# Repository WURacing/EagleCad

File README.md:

View this project on [CADLAB.io](https://cadlab.io/project/1317). 

# EagleCad
Version Control for EagleCad files

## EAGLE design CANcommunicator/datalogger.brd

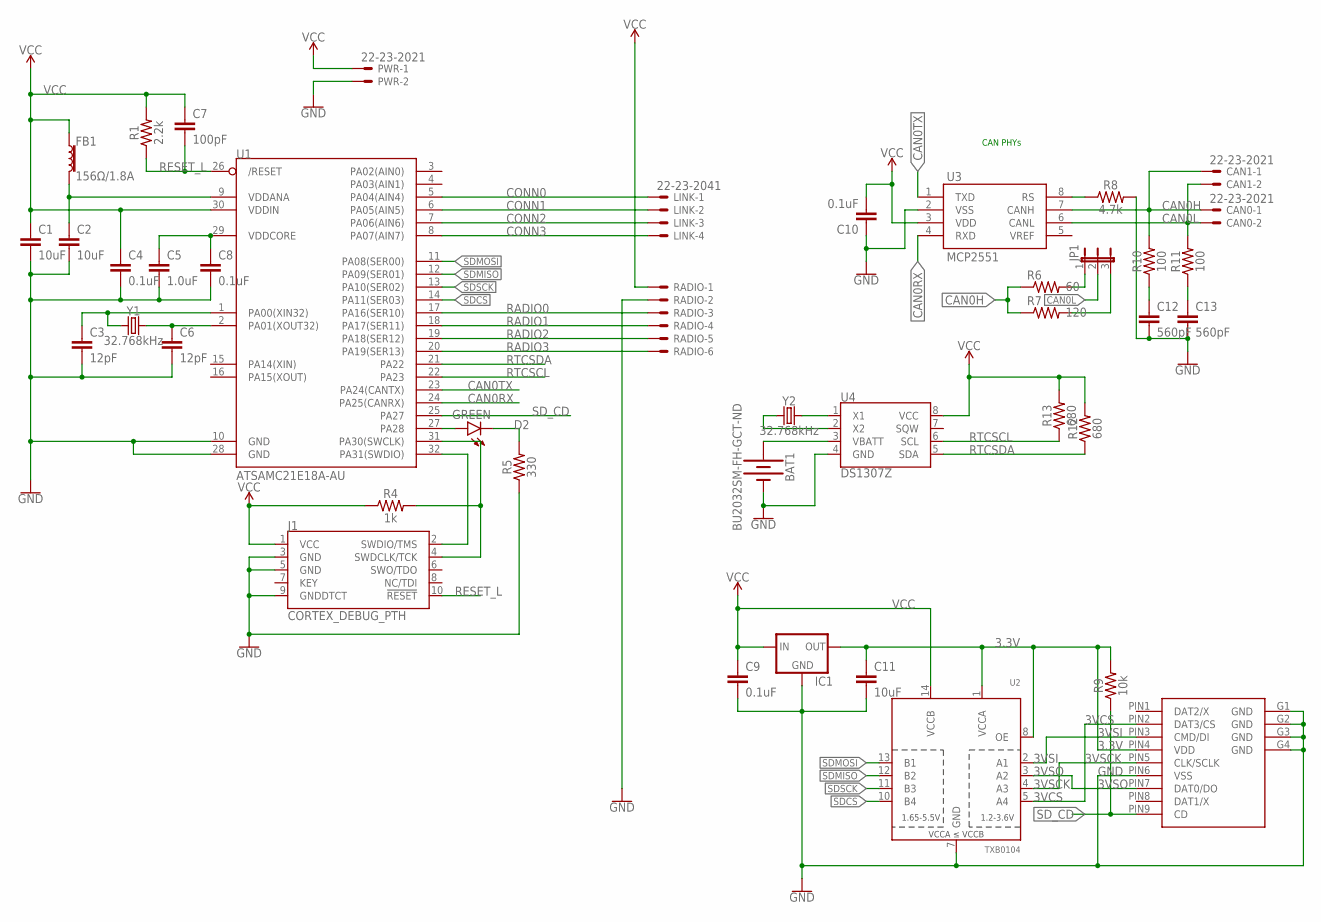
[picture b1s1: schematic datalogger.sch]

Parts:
BAT1: BU2032SM-FH-GCT-ND; BAT_BU2032SM-BT-GTR
C1, C2, C11: 10uF; 0603
C3, C6: 12pF; 0603
C4, C8, C9, C10: 0.1uF; 0603
C5: 1.0uF; 0603
C7: 100pF; 0603
C12, C13: 560pF; 0603
CAN0, CAN1: 22-23-2021
D2: GREEN; LED_3MM
FB1: 156Ω/1.8A; 0603
IC1: 78LXX
J1: CORTEX_DEBUG_PTH; 2X5-PTH-1.27MM
JP1: JP2E; JP2
LINK: 22-23-2041
PWR: 22-23-2021
R1: 2.2k; 0603
R4: 1k; 0603
R5: 330; 0603
R6: 60; R0603
R7: 120; R0603
R8: 4.7k; 0603
R9: 10k; 0603
R10, R11: 100; 0603
R12, R13: 680; 0603
RADIO: 22-23-2061
SD1: WM14405CT-ND; 1051620001-SMD
U1: ATSAMC21E18A-AU; TQFP32-08
U2: TXB0104; TSSOP14
U3: MCP2551; SO08
U4: DS1307Z; SO08-0.15
Y1, Y2: 32.768kHz; CRYSTAL-PTH-2X6-CYL

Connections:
3.3V: C11.1, IC1.OUT, R9.2, SD1.PIN4 (VDD), U2.1 (VCCA), U2.8 (OE)
3VCS: SD1.PIN2 (DAT3/CS), U2.5 (A4)
3VSCK: SD1.PIN5 (CLK/SCLK), U2.4 (A3)
3VSI: SD1.PIN3 (CMD/DI), U2.2 (A1)
3VSO: SD1.PIN7 (DAT0/DO), U2.3 (A2)
C1HRC: C12.1, R10.1
C1LRC: C13.1, R11.1
C1RS: R8.1, U3.8 (RS)
CAN0H: CAN0.1, CAN1.1, R6.1, R7.1, R10.2, U3.7 (CANH)
CAN0L: CAN0.2, CAN1.2, JP1.2, R11.2, U3.6 (CANL)
CAN0RX: U1.24 (PA25(CANRX)), U3.4 (RXD)
CAN0TX: U1.23 (PA24(CANTX)), U3.1 (TXD)
CONN0: LINK.1, U1.5 (PA04(AIN4))
CONN1: LINK.2, U1.6 (PA05(AIN5))
CONN2: LINK.3, U1.7 (PA06(AIN6))
CONN3: LINK.4, U1.8 (PA07(AIN7))
GND: BAT1.2 (-), C1.2, C2.2, C3.2, C4.2, C5.2, C6.2, C8.2, C9.2, C10.1, C11.2, C12.2, C13.2, IC1.GND, J1.3 (GND), J1.5 (GND), J1.9 (GNDDTCT), PWR.2, R5.1, R8.2, RADIO.2, SD1.G1 (GND), SD1.G2 (GND), SD1.G3 (GND), SD1.G4 (GND), SD1.PIN6 (VSS), U1.10 (GND), U1.28 (GND), U2.7 (GND), U3.2 (VSS), U4.4 (GND)
LEDA: D2.A, U1.27 (PA28)
LEDC: D2.K (C), R5.2
unnamed: BAT1.1 (+), U4.3 (VBATT)
unnamed: U4.1 (X1), Y2.2
unnamed: JP1.1, R6.2
unnamed: U4.2 (X2), Y2.1
unnamed: JP1.3, R7.2
RADIO0: RADIO.3, U1.17 (PA16(SER10))
RADIO1: RADIO.4, U1.18 (PA17(SER11))
RADIO2: RADIO.5, U1.19 (PA18(SER12))
RADIO3: RADIO.6, U1.20 (PA19(SER13))
RESET_L: C7.2, J1.10 (!RESET), R1.1, U1.26 (/RESET)
RTCSCL: R13.1, U1.22 (PA23), U4.6 (SCL)
RTCSDA: R12.1, U1.21 (PA22), U4.5 (SDA)
SDCS: U1.14 (PA11(SER03)), U2.10 (B4)
SDMISO: U1.12 (PA09(SER01)), U2.12 (B2)
SDMOSI: U1.11 (PA08(SER00)), U2.13 (B1)
SDSCK: U1.13 (PA10(SER02)), U2.11 (B3)
SD_CD: R9.1, SD1.PIN9 (CD), U1.25 (PA27)
SWDCLK: J1.4 (SWDCLK/TCK), R4.2, U1.31 (PA30(SWCLK))
SWDIO: J1.2 (SWDIO/TMS), U1.32 (PA31(SWDIO))
VCC: C1.1, C4.1, C7.1, C9.1, C10.2, FB1.1, IC1.IN, J1.1 (VCC), PWR.1, R1.2, R4.1, R12.2, R13.2, RADIO.1, U1.30 (VDDIN), U2.14 (VCCB), U3.3 (VDD), U4.8 (VCC)
VDDANA1: C2.1, FB1.2, U1.9 (VDDANA)
VDDCORE: C5.1, C8.1, U1.29 (VDDCORE)
XIN32: C3.1, U1.1 (PA00(XIN32)), Y1.1
XOUT32: C6.1, U1.2 (PA01(XOUT32)), Y1.2

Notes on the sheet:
CAN PHYs

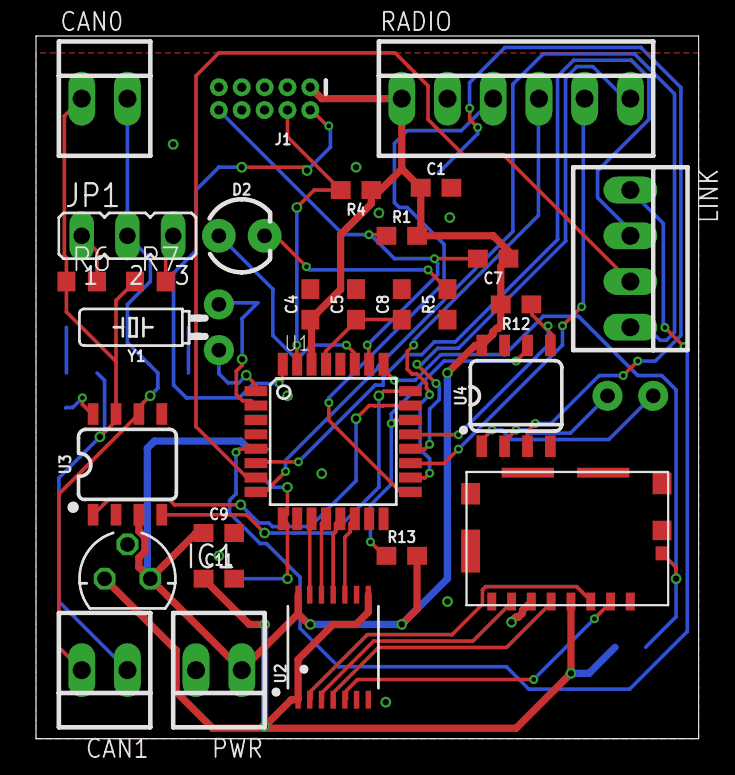
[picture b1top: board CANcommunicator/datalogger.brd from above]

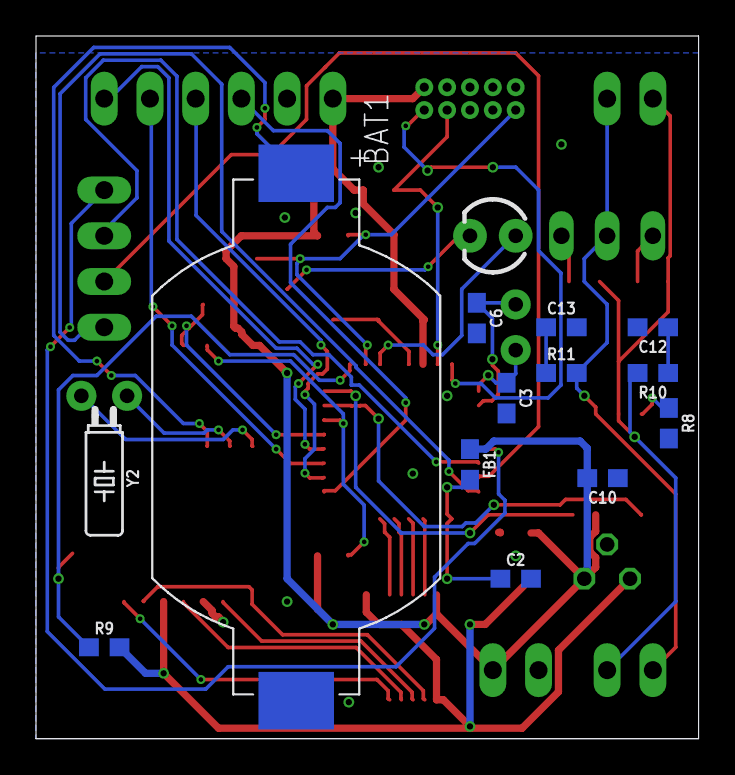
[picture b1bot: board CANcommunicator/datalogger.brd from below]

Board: 2 copper layers, 36.8 x 39.0 mm, 42 parts (13 on the bottom side), 43 nets.

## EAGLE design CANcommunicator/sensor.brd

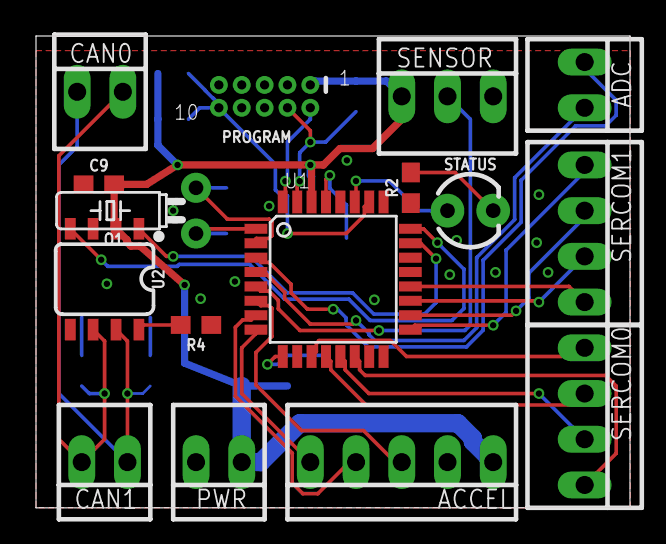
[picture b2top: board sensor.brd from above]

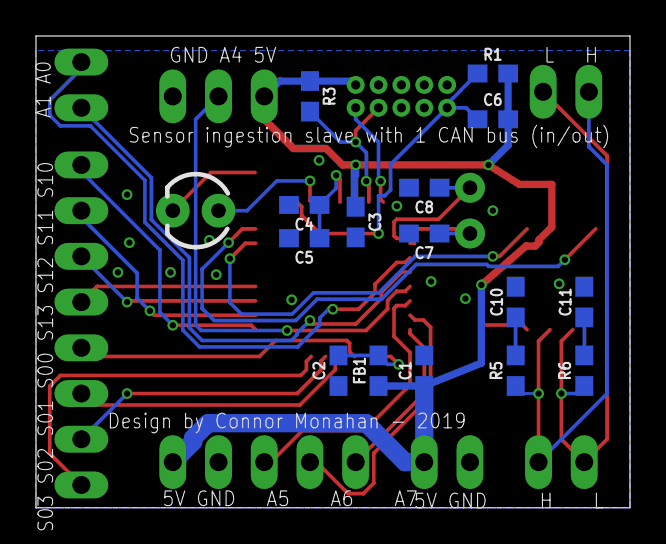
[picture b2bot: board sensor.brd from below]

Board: 2 copper layers, 33.0 x 26.2 mm, 31 parts (15 on the bottom side), 32 nets.

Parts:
ACCEL: 22-23-2051
ADC: 22-23-2021
C1, C2: 10uF; 0603
C3, C5, C9: 0.1uF; 0603
C4: 1.0uF; 0603
C6: 100pF; 0603
C7, C8: 12pF; 0603
C10, C11: 560pF; 0603
CAN0, CAN1: 22-23-2021
FB1: 156Ω/1.8A; 0603
O1: 32.768kHz; CRYSTAL-PTH-2X6-CYL
PROGRAM: CORTEX_DEBUG_PTH; 2X5-PTH-1.27MM
PWR: 22-23-2021
R1: 2.2k; 0603
R2: 330; 0603
R3: 1k; 0603
R4: 4.7k; 0603
R5, R6: 100; 0603
SENSOR: 22-23-2031
SERCOM0, SERCOM1: 22-23-2041
STATUS: GREEN; LED_3MM
U1: ATSAMC21E18A-AU; TQFP32-08
U2: MCP2551; SO08

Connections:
A0: ADC.1, U1.3
A1: ADC.2, U1.4
A4: SENSOR.2, U1.5
A5: ACCEL.3, U1.6
A6: ACCEL.4, U1.7
A7: ACCEL.5, U1.8
C1HRC: C10.1, R5.1
C1LRC: C11.1, R6.1
C1RS: R4.1, U2.8
CAN1H: CAN0.1, CAN1.1, R5.2, U2.7
CAN1L: CAN0.2, CAN1.2, R6.2, U2.6
CAN1RX: U1.24, U2.4
CAN1TX: U1.23, U2.1
GND: ACCEL.2, C1.2, C2.2, C3.2, C4.2, C5.2, C7.2, C8.2, C9.1, C10.2, C11.2, PROGRAM.3, PROGRAM.5, PROGRAM.9, PWR.2, R2.1, R4.2, SENSOR.3, U1.10, U1.28, U2.3
LEDA: STATUS.A, U1.27
LEDC: R2.2, STATUS.K
RESET_L: C6.2, PROGRAM.10, R1.1, U1.26
S00: SERCOM0.1, U1.11
S01: SERCOM0.2, U1.12
S02: SERCOM0.3, U1.13
S03: SERCOM0.4, U1.14
S10: SERCOM1.1, U1.17
S11: SERCOM1.2, U1.18
S12: SERCOM1.3, U1.19
S13: SERCOM1.4, U1.20
SWDCLK: PROGRAM.4, R3.2, U1.31
SWDIO: PROGRAM.2, U1.32
VCC: ACCEL.1, C1.1, C3.1, C6.1, C9.2, FB1.1, PROGRAM.1, PWR.1, R1.2, R3.1, SENSOR.1, U1.30, U2.2
VDDANA: C2.1, FB1.2, U1.9
VDDCORE: C4.1, C5.1, U1.29
XIN32: C7.1, O1.1, U1.1
XOUT32: C8.1, O1.2, U1.2

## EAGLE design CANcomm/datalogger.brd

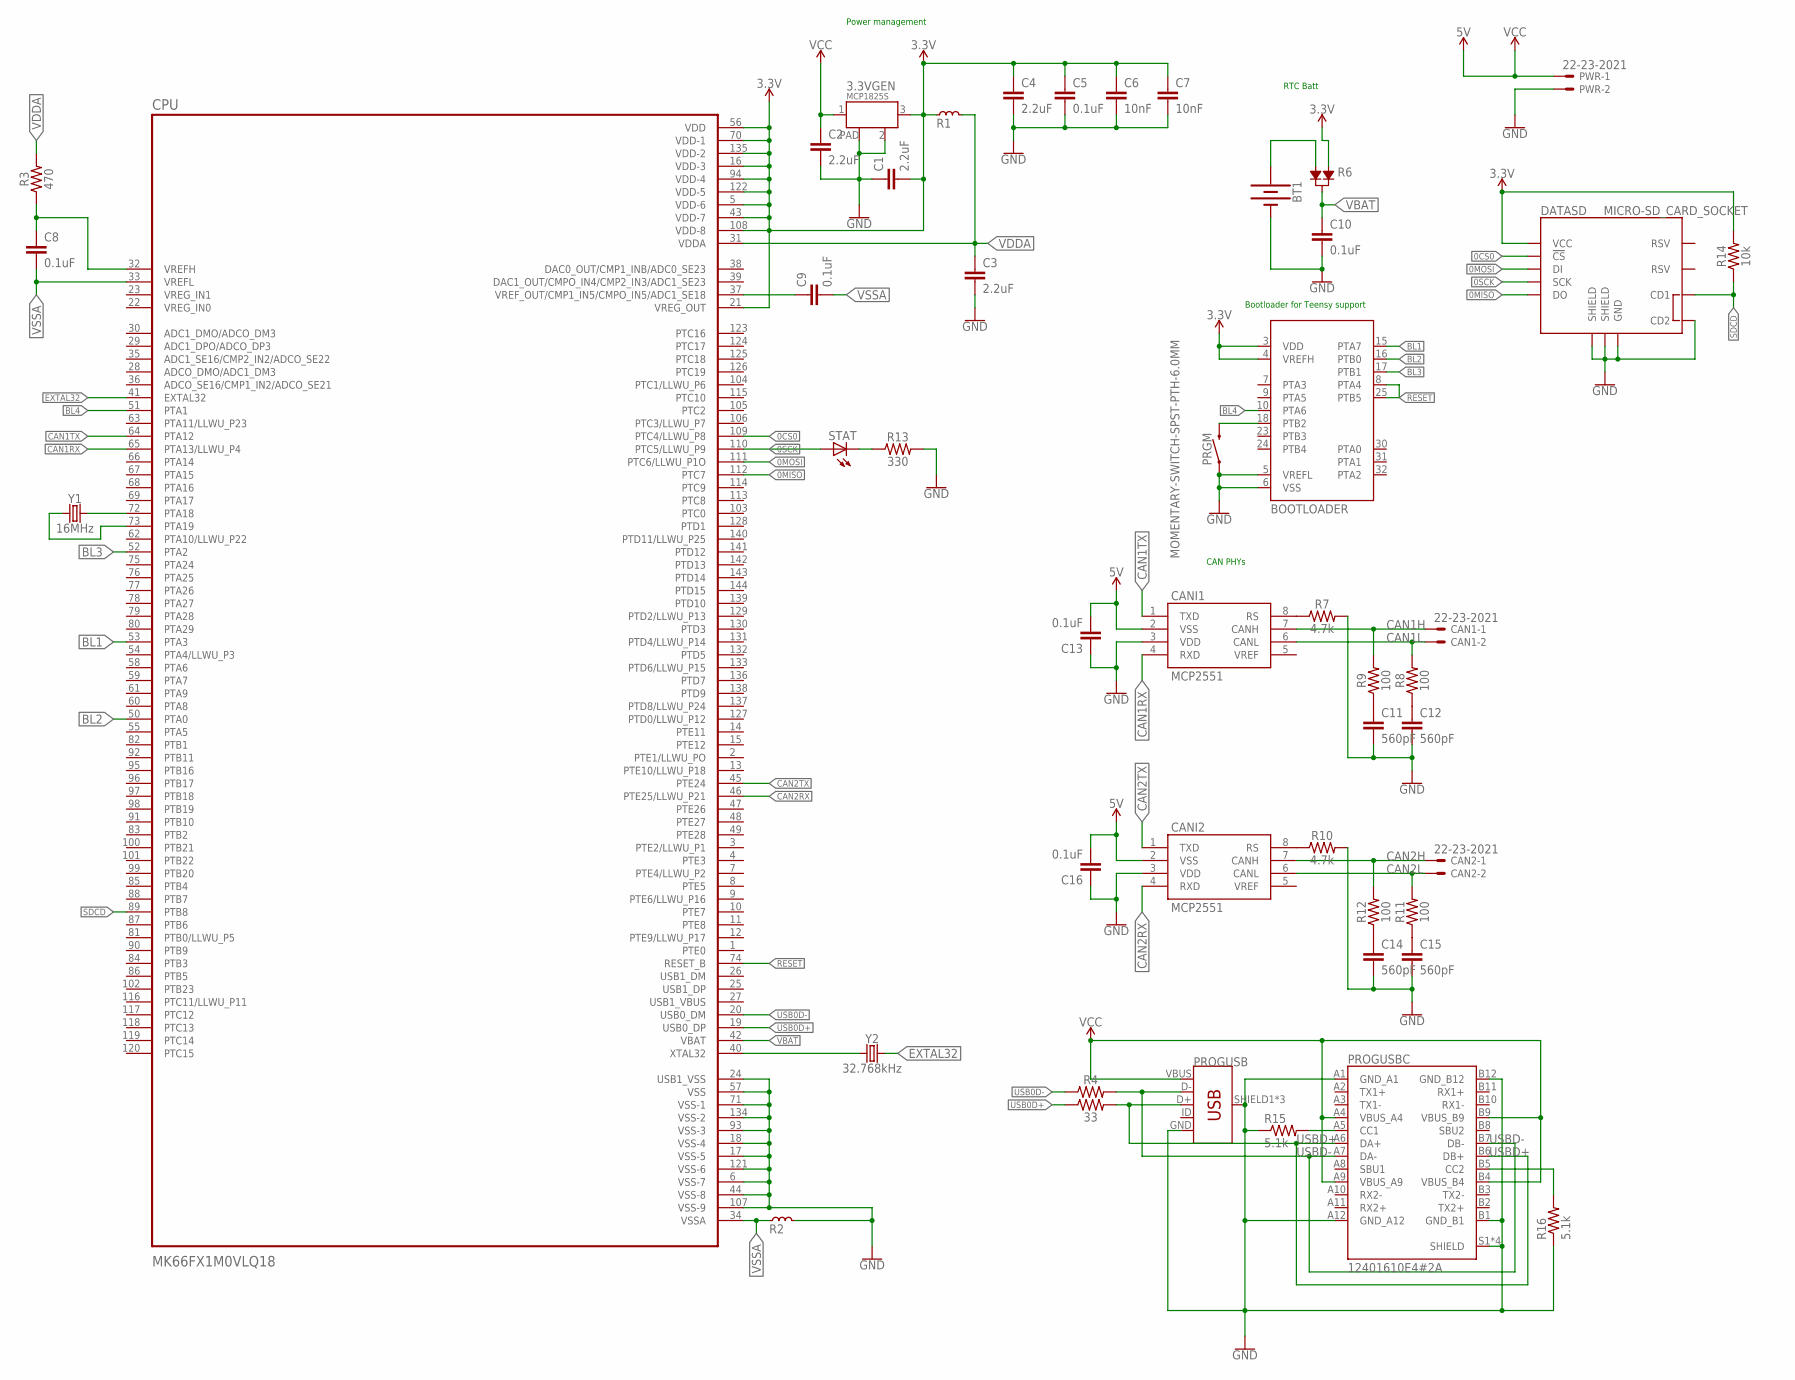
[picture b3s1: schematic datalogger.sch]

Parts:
3.3VGEN: MCP1825S; SOT-223
BOOTLOADER: MKL04Z32VLC4; LQFP32-08
BT1: BATTERY-20MM_SMD_4LEGS; BATTCON_20MM_4LEGS
C1, C2, C3, C4: 2.2uF; 0603
C5, C8, C9, C10, C13, C16: 0.1uF; 0603
C6, C7: 10nF; 0603
C11, C12, C14, C15: 560pF; 0603
CAN1, CAN2: 22-23-2021
CANI1, CANI2: MCP2551; SO08
CPU: MK66FX1M0VLQ18; QFP50P2200X2200X160-144N
DATASD: MICRO-SD_CARD_SOCKET; MICRO-SD-SOCKET
PRGM: MOMENTARY-SWITCH-SPST-PTH-6.0MM; TACTILE_SWITCH_PTH_6.0MM
PROGUSB: USB_MICRO-B_FEMALE-SMT; USB-B-MICRO-SMD
PROGUSBC: 12401610E4#2A; AMPHENOL_12401610E4#2A
PWR: 22-23-2021
R1, R2: FERRITE; L0603
R3: 470; 0603
R4, R5: 33; 0603
R6: DIODE_DUAL; SOT-23
R7, R10: 4.7k; 0603
R8, R9, R11, R12: 100; 0603
R13: 330; 0603
R14: 10k; 0603
R15, R16: 5.1k; R0603
STAT: LED5MM
Y1: 16MHz; CRYSTAL-SMD-5X3.2-4PAD
Y2: 32.768kHz; CRYSTAL-PTH-2X6-CYL

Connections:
0CS0: CPU.109 (PTC4/LLWU_P8), DATASD.CS (!CS)
0MISO: CPU.112 (PTC7), DATASD.DO
0MOSI: CPU.111 (PTC6/LLWU_P1O), DATASD.DI
0SCK: CPU.110 (PTC5/LLWU_P9), DATASD.SCLK (SCK), STAT.A
3.3V: 3.3VGEN.3 (OUT), BOOTLOADER.3 (VDD), BOOTLOADER.4 (VREFH), C1.2, C4.1, C5.1, C6.1, C7.1, CPU.5 (VDD-6), CPU.16 (VDD-3), CPU.21 (VREG_OUT), CPU.43 (VDD-7), CPU.56 (VDD), CPU.70 (VDD-1), CPU.94 (VDD-4), CPU.108 (VDD-8), CPU.122 (VDD-5), CPU.135 (VDD-2), DATASD.VCC, R1.1, R6.2, R14.2
5V: C13.2, C16.2, CANI1.2 (VSS), CANI2.2 (VSS)
BL1: BOOTLOADER.15 (PTA7), CPU.53 (PTA3)
BL2: BOOTLOADER.16 (PTB0), CPU.50 (PTA0)
BL3: BOOTLOADER.17 (PTB1), CPU.52 (PTA2)
BL4: BOOTLOADER.10 (PTA6), CPU.51 (PTA1)
CAN1H: CAN1.1, CANI1.7 (CANH), R9.2
CAN1L: CAN1.2, CANI1.6 (CANL), R8.2
CAN1RX: CANI1.4 (RXD), CPU.65 (PTA13/LLWU_P4)
CAN1TX: CANI1.1 (TXD), CPU.64 (PTA12)
CAN2H: CAN2.1, CANI2.7 (CANH), R12.2
CAN2L: CAN2.2, CANI2.6 (CANL), R11.2
CAN2RX: CANI2.4 (RXD), CPU.46 (PTE25/LLWU_P21)
CAN2TX: CANI2.1 (TXD), CPU.45 (PTE24)
EXTAL32: CPU.41 (EXTAL32), Y2.2
GND: 3.3VGEN.2 (GND), 3.3VGEN.PAD, BOOTLOADER.5 (VREFL), BOOTLOADER.6 (VSS), BT1.NEGATIVE (-), C1.1, C2.2, C3.2, C4.2, C5.2, C6.2, C7.2, C10.2, C11.2, C12.2, C13.1, C14.2, C15.2, C16.1, CANI1.3 (VDD), CANI2.3 (VDD), CPU.6 (VSS-7), CPU.17 (VSS-5), CPU.18 (VSS-4), CPU.24 (USB1_VSS), CPU.44 (VSS-8), CPU.57 (VSS), CPU.71 (VSS-1), CPU.93 (VSS-3), CPU.107 (VSS-9), CPU.121 (VSS-6), CPU.134 (VSS-2), DATASD.CD2, DATASD.GND, DATASD.GND1 (SHIELD), DATASD.GND3 (SHIELD), PRGM.1, PROGUSB.GND, PROGUSB.SHIELD1 (SHIELD), PROGUSB.SHIELD2 (SHIELD), PROGUSB.SHIELD3 (SHIELD), PROGUSBC.A1 (GND_A1), PROGUSBC.A12 (GND_A12), PROGUSBC.B1 (GND_B1), PROGUSBC.B12 (GND_B12), PROGUSBC.S1 (SHIELD), PROGUSBC.S2 (SHIELD), PROGUSBC.S3 (SHIELD), PROGUSBC.S4 (SHIELD), PWR.2, R2.2, R7.2, R10.2, R13.2, R15.1, R16.1
unnamed: CPU.72 (PTA18), Y1.3 (2)
unnamed: CPU.73 (PTA19), Y1.1
unnamed: CPU.40 (XTAL32), Y2.1
unnamed: C9.1, CPU.37 (VREF_OUT/CMP1_IN5/CMPO_IN5/ADC1_SE18)
unnamed: R13.1, STAT.K (C)
unnamed: PROGUSBC.A5 (CC1), R15.2
unnamed: BT1.POSITIVE@1 (+), BT1.POSITIVE@2 (+), BT1.POSITIVE@3 (+), BT1.POSITIVE@4 (+), R6.1
unnamed: PROGUSBC.B5 (CC2), R16.2
unnamed: CANI1.8 (RS), R7.1
unnamed: C11.1, R9.1
unnamed: C12.1, R8.1
unnamed: CANI2.8 (RS), R10.1
unnamed: C14.1, R12.1
unnamed: C15.1, R11.1
PRGM: BOOTLOADER.18 (PTB2), PRGM.3 (2)
RESET: BOOTLOADER.8 (PTA4), BOOTLOADER.25 (PTB5), CPU.74 (RESET_B)
SDCD: CPU.89 (PTB8), DATASD.CD1, R14.1
USB0D+: CPU.19 (USB0_DP), R5.1
USB0D-: CPU.20 (USB0_DM), R4.1
USBD+: PROGUSB.D+, PROGUSBC.A6 (DA+), PROGUSBC.B6 (DB+), R5.2
USBD-: PROGUSB.D-, PROGUSBC.A7 (DA-), PROGUSBC.B7 (DB-), R4.2
VBAT: C10.1, CPU.42 (VBAT), R6.3
VCC: 3.3VGEN.1 (IN), C2.1, PROGUSB.VBUS, PROGUSBC.A4 (VBUS_A4), PROGUSBC.A9 (VBUS_A9), PROGUSBC.B4 (VBUS_B4), PROGUSBC.B9 (VBUS_B9), PWR.1
VDDA: C3.1, CPU.31 (VDDA), R1.2, R3.2
VREFH: C8.1, CPU.32 (VREFH), R3.1
VSSA: C8.2, C9.2, CPU.33 (VREFL), CPU.34 (VSSA), R2.1

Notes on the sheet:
Power management
CAN PHYs
Bootloader for Teensy support
RTC Batt

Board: 2 copper layers, 48 parts (21 on the bottom side), 46 nets, no tracks yet.

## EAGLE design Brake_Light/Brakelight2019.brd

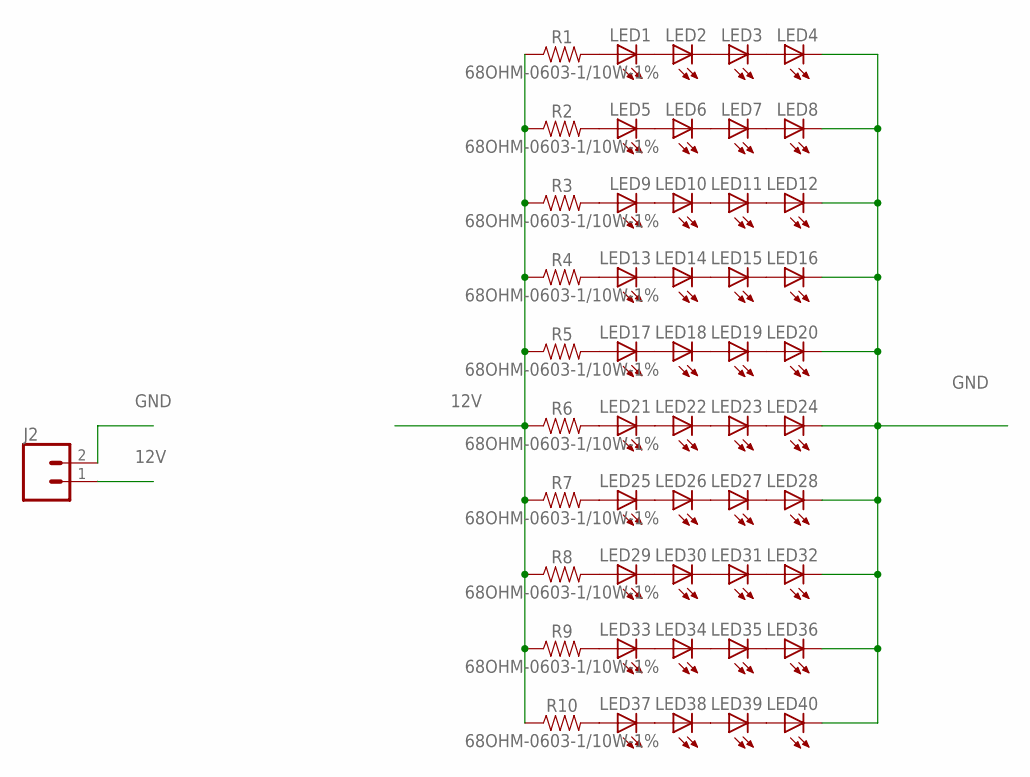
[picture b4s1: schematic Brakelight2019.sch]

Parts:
J2: CONN_02POLAR; MOLEX-1X2
LED1, LED2, LED3, LED4, LED5, LED6, LED7, LED8, LED9, LED10, LED11, LED12, LED13, LED14, LED15, LED16, LED17, LED18, LED19, LED20, LED21, LED22, LED23, LED24, LED25, LED26, LED27, LED28, LED29, LED30, LED31, LED32, LED33, LED34, LED35, LED36, LED37, LED38, LED39, LED40: LED5MM
R1, R2, R3, R4, R5, R6, R7, R8, R9, R10: 68OHM-0603-1/10W-1%; 0603

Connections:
12V: J2.1, R1.1, R2.1, R3.1, R4.1, R5.1, R6.1, R7.1, R8.1, R9.1, R10.1
GND: J2.2, LED4.K (C), LED8.K (C), LED12.K (C), LED16.K (C), LED20.K (C), LED24.K (C), LED28.K (C), LED32.K (C), LED36.K (C), LED40.K (C)
unnamed: LED1.A, R1.2
unnamed: LED1.K (C), LED2.A
unnamed: LED2.K (C), LED3.A
unnamed: LED3.K (C), LED4.A
unnamed: LED5.A, R2.2
unnamed: LED5.K (C), LED6.A
unnamed: LED6.K (C), LED7.A
unnamed: LED7.K (C), LED8.A
unnamed: LED9.A, R3.2
unnamed: LED9.K (C), LED10.A
unnamed: LED10.K (C), LED11.A
unnamed: LED11.K (C), LED12.A
unnamed: LED13.A, R4.2
unnamed: LED13.K (C), LED14.A
unnamed: LED14.K (C), LED15.A
unnamed: LED15.K (C), LED16.A
unnamed: LED17.A, R5.2
unnamed: LED17.K (C), LED18.A
unnamed: LED18.K (C), LED19.A
unnamed: LED19.K (C), LED20.A
unnamed: LED21.A, R6.2
unnamed: LED21.K (C), LED22.A
unnamed: LED22.K (C), LED23.A
unnamed: LED23.K (C), LED24.A
unnamed: LED25.A, R7.2
unnamed: LED25.K (C), LED26.A
unnamed: LED26.K (C), LED27.A
unnamed: LED27.K (C), LED28.A
unnamed: LED29.A, R8.2
unnamed: LED29.K (C), LED30.A
unnamed: LED30.K (C), LED31.A
unnamed: LED31.K (C), LED32.A
unnamed: LED33.A, R9.2
unnamed: LED33.K (C), LED34.A
unnamed: LED34.K (C), LED35.A
unnamed: LED35.K (C), LED36.A
unnamed: LED37.A, R10.2
unnamed: LED37.K (C), LED38.A
unnamed: LED38.K (C), LED39.A
unnamed: LED39.K (C), LED40.A

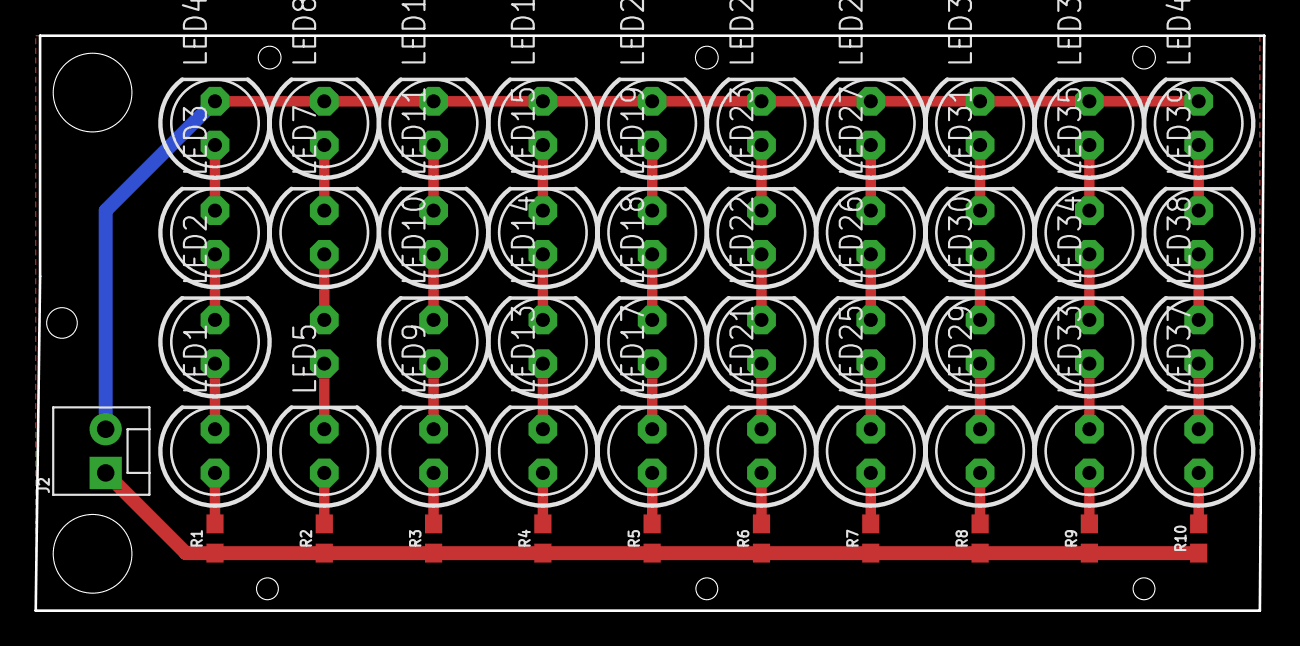
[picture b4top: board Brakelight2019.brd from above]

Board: 2 copper layers, 71.4 x 33.4 mm, 51 parts (1 on the bottom side), 42 nets.

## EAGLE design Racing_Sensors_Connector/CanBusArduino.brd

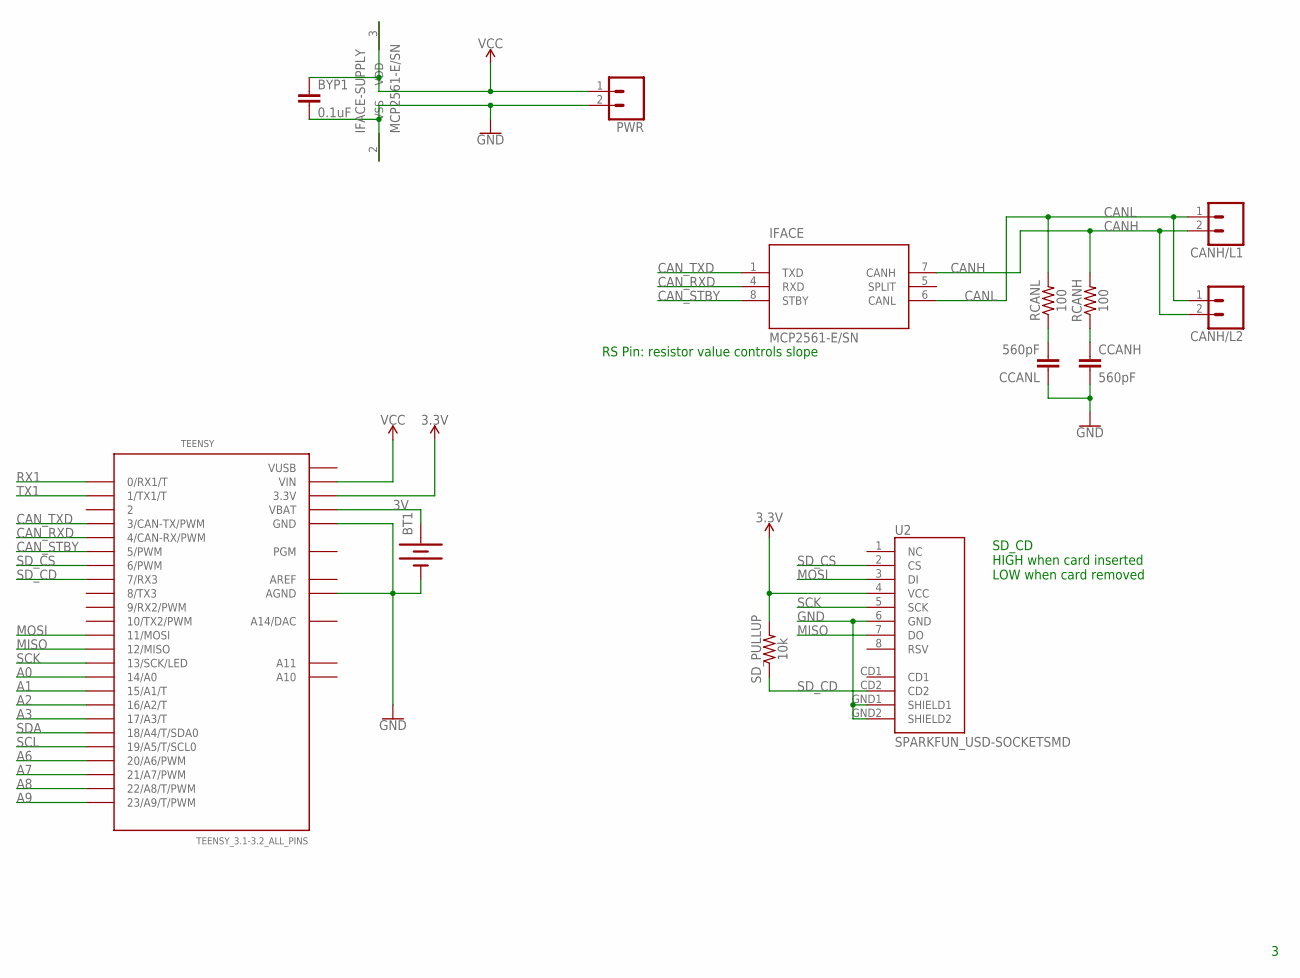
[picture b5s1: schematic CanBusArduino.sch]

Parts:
BT1: BATTERY-20MM_SMD_4LEGS; BATTCON_20MM_4LEGS
BYP1: 0.1uF; 0603
CANH/L1, CANH/L2: CONN_02POLAR; MOLEX-1X2
CCANH: 560pF; 0603
CCANL: 560pF; 0603
IFACE: MCP2561-E/SN; SOIC-8
PWR: CONN_02POLAR; MOLEX-1X2
RCANH: 100; 0603
RCANL: 100; 0603
SD_PULLUP: 10k; 0603
TEENSY: TEENSY_3.1-3.2_ALL_PINS; TEENSY_3.0-3.2&LC_ALL_PINS
U2: SPARKFUN_USD-SOCKETSMD; SPARKFUN_MICRO-SD-SOCKET-PP

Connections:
3.3V: SD_PULLUP.2, TEENSY.3.3V, TEENSY.3.3V1 (3.3V), U2.4 (VCC)
3V: BT1.POSITIVE@1 (+), BT1.POSITIVE@2 (+), BT1.POSITIVE@3 (+), BT1.POSITIVE@4 (+), TEENSY.VBAT
A0: TEENSY.14/A0
A1: TEENSY.15/A1 (15/A1/T)
A2: TEENSY.16/A2 (16/A2/T)
A3: TEENSY.17/A3 (17/A3/T)
A6: TEENSY.20/A6 (20/A6/PWM)
A7: TEENSY.21/A7 (21/A7/PWM)
A8: TEENSY.22/A8 (22/A8/T/PWM)
A9: TEENSY.23/A9 (23/A9/T/PWM)
AREF: TEENSY.AREF
CANH: CANH/L1.2, CANH/L2.2, IFACE.7 (CANH), RCANH.2
CANL: CANH/L1.1, CANH/L2.1, IFACE.6 (CANL), RCANL.2
CAN_RXD: IFACE.4 (RXD), TEENSY.4 (4/CAN-RX/PWM)
CAN_STBY: IFACE.8 (STBY), TEENSY.5 (5/PWM)
CAN_TXD: IFACE.1 (TXD), TEENSY.3 (3/CAN-TX/PWM)
GND: BT1.NEGATIVE (-), BYP1.2, CCANH.2, CCANL.1, IFACE.2 (VSS), PWR.2, TEENSY.AGND, TEENSY.GND, TEENSY.GND1 (GND), U2.6 (GND), U2.GND1 (SHIELD1), U2.GND2 (SHIELD2)
MISO: TEENSY.12 (12/MISO), U2.7 (DO)
MOSI: TEENSY.11 (11/MOSI), U2.3 (DI)
unnamed: CCANL.2, RCANL.1
unnamed: CCANH.1, RCANH.1
RX1: TEENSY.0 (0/RX1/T)
SCK: TEENSY.13 (13/SCK/LED), U2.5 (SCK)
SCL: TEENSY.19/A5 (19/A5/T/SCL0)
SDA: TEENSY.18/A4 (18/A4/T/SDA0)
SD_CD: SD_PULLUP.1, TEENSY.7 (7/RX3), U2.CD2
SD_CS: TEENSY.6 (6/PWM), U2.2 (CS)
TX1: TEENSY.1 (1/TX1/T)
VCC: BYP1.1, IFACE.3 (VDD), PWR.1, TEENSY.VIN
VUSB: TEENSY.VUSB

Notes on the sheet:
SD_CD HIGH when card inserted LOW when card removed
RS Pin: resistor value controls slope

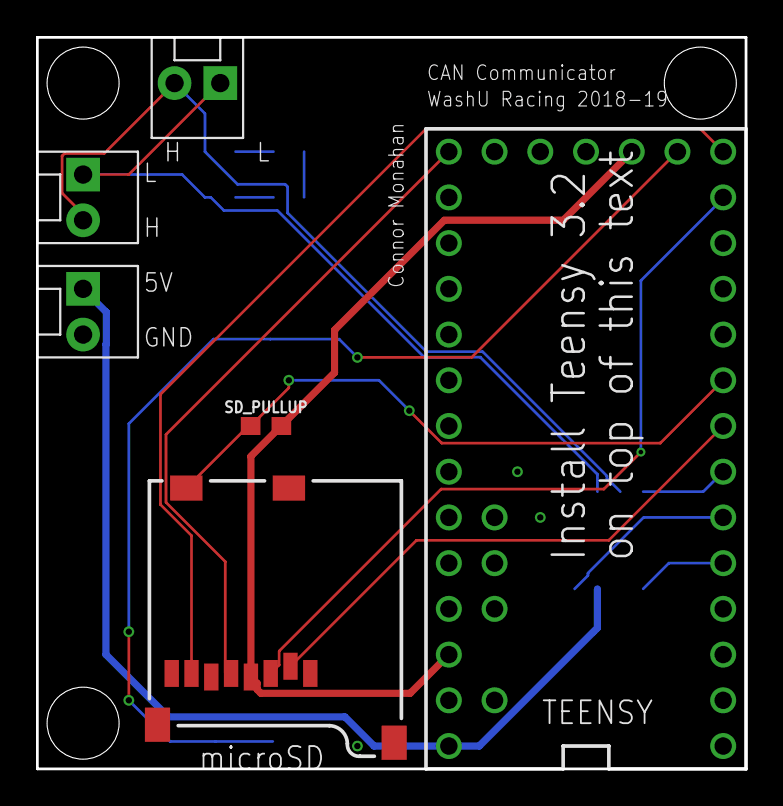
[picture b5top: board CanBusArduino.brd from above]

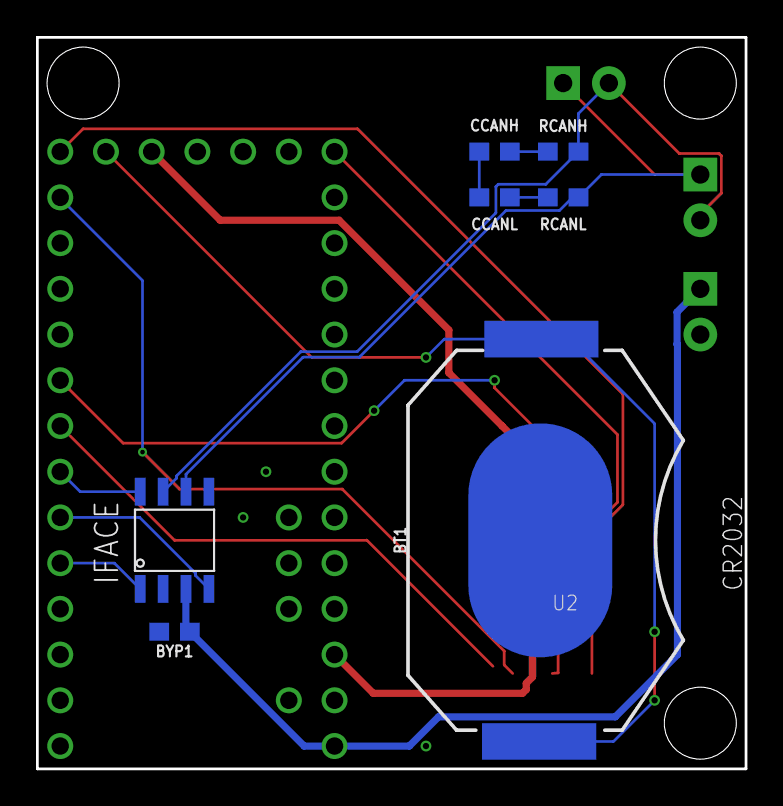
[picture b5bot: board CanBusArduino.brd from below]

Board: 2 copper layers, 39.4 x 40.6 mm, 13 parts (7 on the bottom side), 16 nets.

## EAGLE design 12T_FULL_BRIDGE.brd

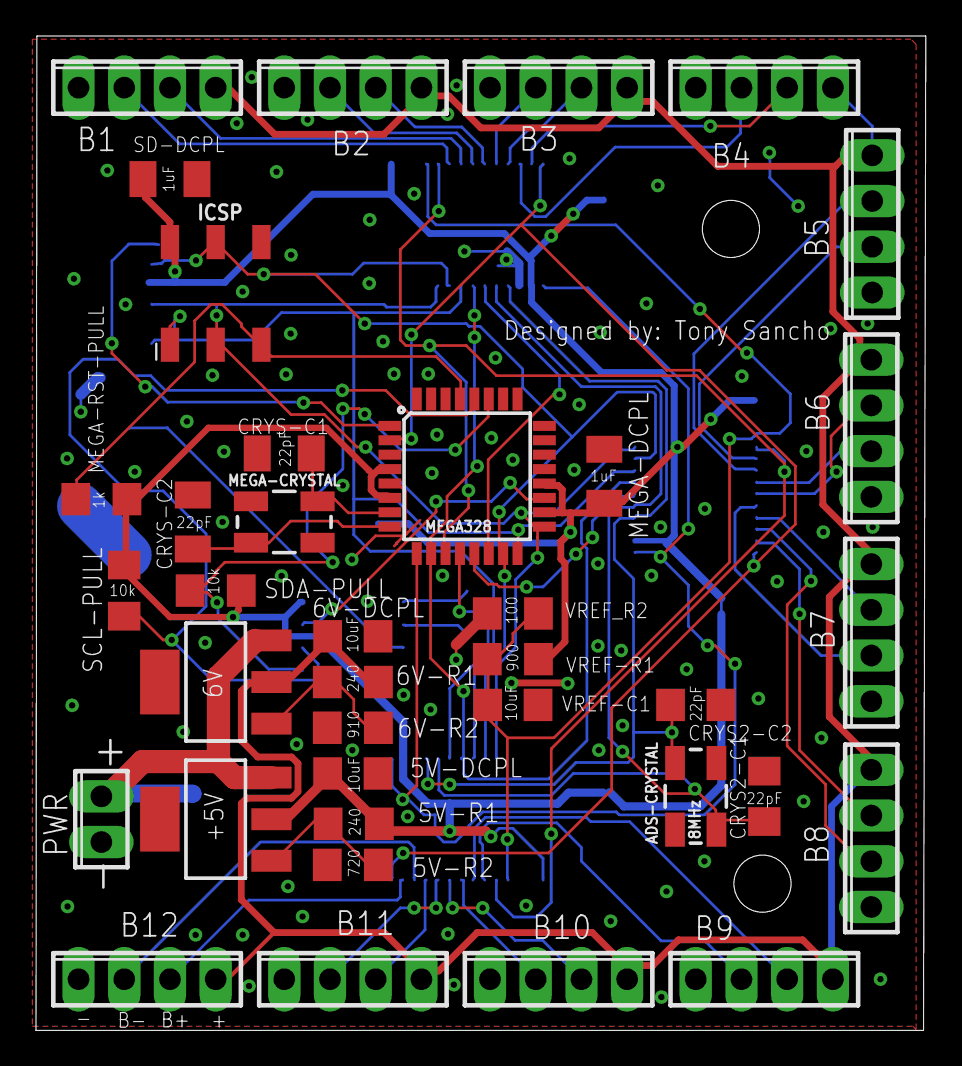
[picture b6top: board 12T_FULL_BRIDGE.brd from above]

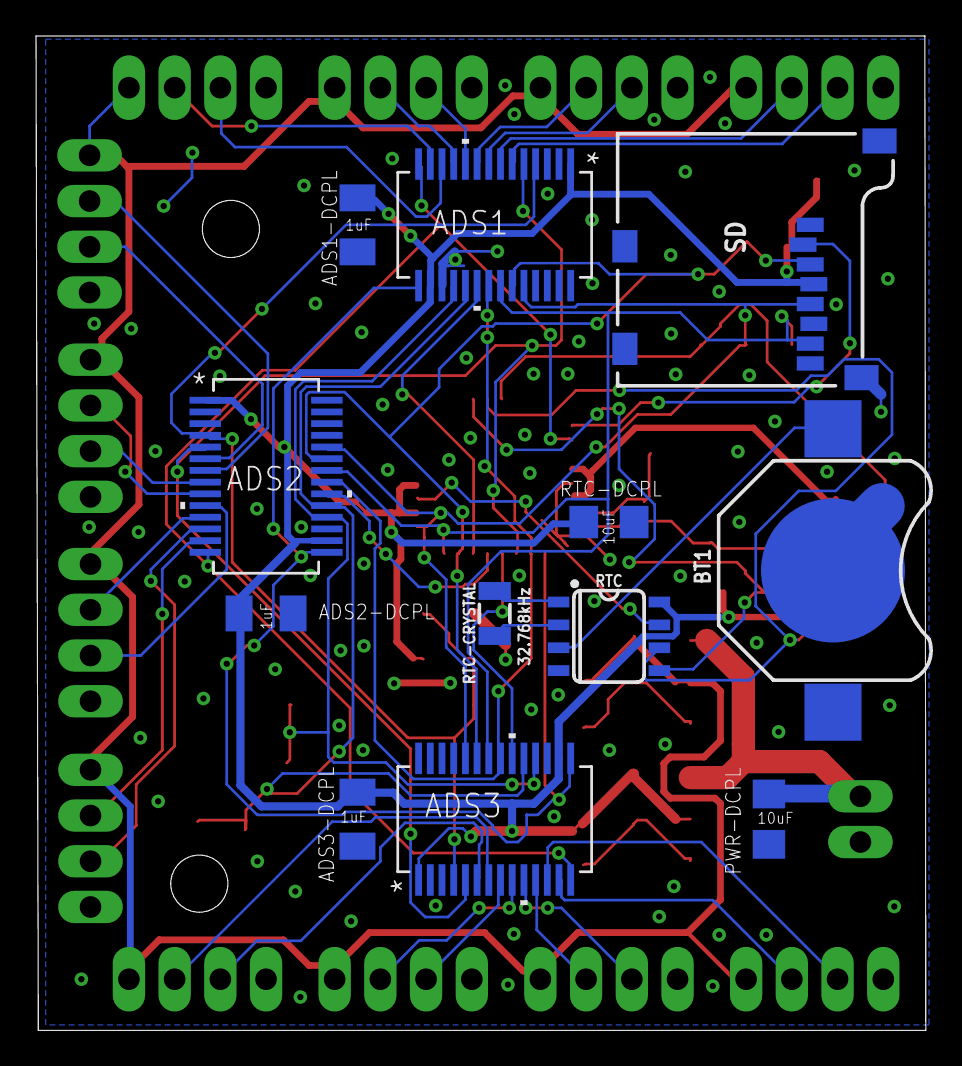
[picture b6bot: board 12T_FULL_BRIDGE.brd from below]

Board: 2 copper layers, 49.4 x 55.2 mm, 49 parts (12 on the bottom side), 53 nets.

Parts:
5V-DCPL, 6V-DCPL: 10uF; C1206
5V-R1, 6V-R1: 240; R1206
5V-R2: 720; R1206
6V-R2: 910; R1206
+5V: V_REG_317SMD; SOT223
ADS1, ADS2, ADS3: ADS1256IDBRDB28-L; DB28-L
ADS1-DCPL, ADS2-DCPL, ADS3-DCPL: 1uF; C1206K
ADS-CRYSTAL: 8MHz; CRYSTAL-SMD-5X3.2-4PAD
B1, B2, B3, B4, B5, B6, B7, B8, B9, B10, B11, B12: 4POL254
BT1: BATTCON_12MM
CRYS2-C1, CRYS2-C2: 22pF; C1206
CRYS-C1, CRYS-C2: 22pF; C1206K
GAUGE: V_REG_317SMD; SOT223
ICSP: 2X3_SMD
MEGA328: ATMEGA328P_TQFP; TQFP32-08
MEGA-CRYSTAL: 16MHz; CRYSTAL-SMD-5X3.2-4PAD
MEGA-DCPL: 1uF; C1206K
MEGA-RST-PULL: 1k; R1206
PWR: 2POL254
PWR-DCPL: 10uF; C1206
RTC: DS1307Z; SO08-0.15
RTC-CRYSTAL: 32.768kHz; CRYSTAL-SMD-3.2X1.5MM
RTC-DCPL: 10uF; C1206
SCL-PULL: 10k; R1206
SD: MICRO-SD_CARD_SOCKET; MICRO-SD-SOCKET
SD-DCPL: 1uF; C1206K
SDA-PULL: 10k; R1206
VREF-C1: 10uF; C1206
VREF-R1: 900; R1206
VREF_R2: 100; R1206

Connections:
+3V: BT1.PWR@1, RTC.3
+5V: 5V-DCPL.1, 5V-R1.2, +5V.2, ADS1.1, ADS1.16, ADS1-DCPL.1, ADS2.1, ADS2.16, ADS2-DCPL.1, ADS3.1, ADS3.16, ADS3-DCPL.1, ICSP.2, MEGA328.4, MEGA328.6, MEGA328.18, MEGA328.20, MEGA-DCPL.1, MEGA-RST-PULL.2, RTC.8, RTC-DCPL.1, SCL-PULL.2, SD.VCC, SD-DCPL.1, SDA-PULL.2, VREF-R1.2
+12V: +5V.3, GAUGE.3, PWR.2, PWR-DCPL.2
ADS1-CS: ADS1.20, MEGA328.14
ADS2-CS: ADS2.20, MEGA328.13
ADS3-CS: ADS3.20, MEGA328.12
ADS-DRDY: ADS1.21, ADS2.21, ADS3.21, MEGA328.10
ADS-RESET: ADS1.15, ADS2.15, ADS3.15, MEGA328.9
ADS-SYNC: ADS1.14, ADS2.14, ADS3.14, MEGA328.2
ADS-XTAL1: ADS1.19, ADS2.19, ADS3.19, ADS-CRYSTAL.1, CRYS2-C1.1
ADS-XTAL2: ADS1.18, ADS2.18, ADS3.18, ADS-CRYSTAL.3, CRYS2-C2.1
AINCOM: ADS1.5, ADS2.5, ADS3.5, MEGA328.11
B1+: ADS1.7, B1.3
B1-: ADS1.6, B1.2
B2+: ADS1.9, B2.3
B2-: ADS1.8, B2.2
B3+: ADS1.11, B3.3
B3-: ADS1.10, B3.2
B4+: ADS1.13, B4.3
B4-: ADS1.12, B4.2
B5+: ADS2.7, B5.3
B5-: ADS2.6, B5.2
B6+: ADS2.9, B6.3
B6-: ADS2.8, B6.2
B7+: ADS2.11, B7.3
B7-: ADS2.10, B7.2
B8+: ADS2.13, B8.3
B8-: ADS2.12, B8.2
B9+: ADS3.7, B9.3
B9-: ADS3.6, B9.2
B10+: ADS3.9, B10.3
B10-: ADS3.8, B10.2
B11+: ADS3.11, B11.3
B11-: ADS3.10, B11.2
B12+: ADS3.13, B12.3
B12-: ADS3.12, B12.2
GND: 5V-DCPL.2, 5V-R2.1, 6V-DCPL.2, 6V-R2.1, ADS1.2, ADS1.3, ADS1.17, ADS1-DCPL.2, ADS2.2, ADS2.3, ADS2.17, ADS2-DCPL.2, ADS3.2, ADS3.3, ADS3.17, ADS3-DCPL.2, B1.1, B2.1, B3.1, B4.1, B5.1, B6.1, B7.1, B8.1, B9.1, B10.1, B11.1, B12.1, BT1.GND, CRYS2-C1.2, CRYS2-C2.2, CRYS-C1.1, CRYS-C2.2, ICSP.6, MEGA328.3, MEGA328.5, MEGA328.21, MEGA-DCPL.2, PWR.1, PWR-DCPL.1, RTC.4, RTC-DCPL.2, SD.CD1, SD.CD2, SD.GND, SD.GND1, SD.GND3, SD-DCPL.2, VREF-C1.2, VREF_R2.1
MEGA-RESET: ICSP.5, MEGA328.29, MEGA-RST-PULL.1
MEGA-XTAL1: CRYS-C1.2, MEGA328.7, MEGA-CRYSTAL.3
MEGA-XTAL2: CRYS-C2.1, MEGA328.8, MEGA-CRYSTAL.1
MISO: ADS1.22, ADS2.22, ADS3.22, ICSP.1, MEGA328.16, SD.DO
MOSI: ADS1.23, ADS2.23, ADS3.23, ICSP.4, MEGA328.15, SD.DI
unnamed: 5V-R1.1, 5V-R2.2, +5V.1
unnamed: 6V-R1.1, 6V-R2.2, GAUGE.1
unnamed: RTC.1, RTC-CRYSTAL.P$2
unnamed: RTC.2, RTC-CRYSTAL.P$1
SCK: ADS1.24, ADS2.24, ADS3.24, ICSP.3, MEGA328.17, SD.SCLK
SCL: MEGA328.28, RTC.6, SCL-PULL.1
SD-CS: MEGA328.1, SD.CS
SDA: MEGA328.27, RTC.5, SDA-PULL.1
SQW: MEGA328.19, RTC.7
VCC: 6V-DCPL.1, 6V-R1.2, B1.4, B2.4, B3.4, B4.4, B5.4, B6.4, B7.4, B8.4, B9.4, B10.4, B11.4, B12.4, GAUGE.2
VREF: ADS1.4, ADS2.4, ADS3.4, VREF-C1.1, VREF-R1.1, VREF_R2.2

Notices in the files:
parts and their libraries:
SparkFun-LED: Licensing: Creative Commons ShareAlike 4.0 International - https://creativecommons.org/licenses/by-sa/4.0
Volks73-MicrochipTechnology: Creative Commons Attribution-ShareAlike 3.0 Unported (CC BY-SA 3.0), http://creativecommons.org/licenses/by-sa/3.0/.
